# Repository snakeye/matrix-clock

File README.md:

matrix-clock
============

Bedroom clock using 8x8 LED matrix display

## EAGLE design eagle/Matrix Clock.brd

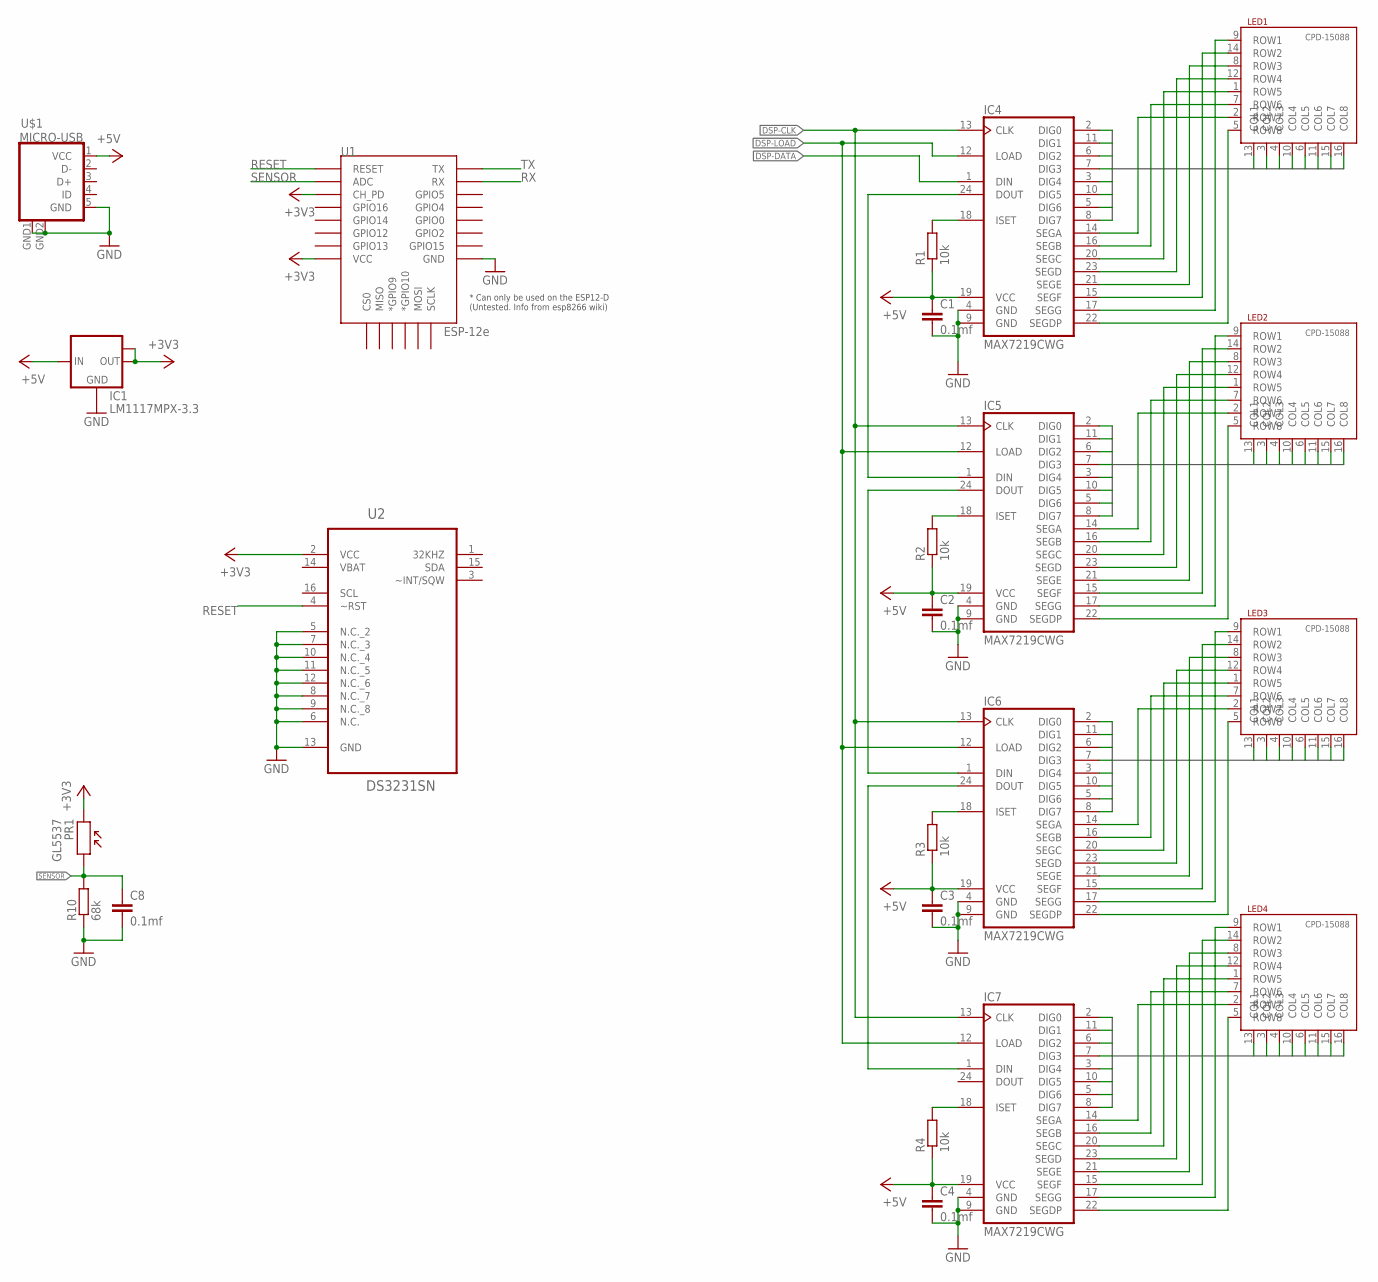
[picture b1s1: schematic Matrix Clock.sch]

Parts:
C1, C2, C3, C4, C8: 0.1mf; C0805
IC1: LM1117MPX-3.3; SOT223
IC4, IC5, IC6, IC7: MAX7219CWG; SO24L
LED1, LED2, LED3, LED4: CPD-15088YGD2/A; CPD15088
PR1: GL5537; GL55
R1, R2, R3, R4: 10k; R0805
R10: 68k; R0805
U1: ESP-12e; ESP12E-SMD
U2: DS3231SN; SOIC127P1032X265-16N
U$1: MICRO-USB

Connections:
+3V3: IC1.2 (OUT), IC1.TAB (OUT1), PR1.P$1, U1.CH_PD, U1.VCC, U2.2 (VCC)
+5V: C1.1, C2.1, C3.1, C4.1, IC1.3 (IN), IC4.19 (VCC), IC5.19 (VCC), IC6.19 (VCC), IC7.19 (VCC), R1.1, R2.1, R3.1, R4.1, U$1.1 (VCC)
C0: IC4.2 (DIG0), LED1.13 (COL1)
C1: IC4.11 (DIG1), LED1.3 (COL2)
C2: IC4.6 (DIG2), LED1.4 (COL3)
C3: IC4.7 (DIG3), LED1.10 (COL4)
C4: IC4.3 (DIG4), LED1.6 (COL5)
C5: IC4.10 (DIG5), LED1.11 (COL6)
C6: IC4.5 (DIG6), LED1.15 (COL7)
C7: IC4.8 (DIG7), LED1.16 (COL8)
C8: IC5.2 (DIG0), LED2.13 (COL1)
C9: IC5.11 (DIG1), LED2.3 (COL2)
C10: IC5.6 (DIG2), LED2.4 (COL3)
C11: IC5.7 (DIG3), LED2.10 (COL4)
C12: IC5.3 (DIG4), LED2.6 (COL5)
C13: IC5.10 (DIG5), LED2.11 (COL6)
C14: IC5.5 (DIG6), LED2.15 (COL7)
C15: IC5.8 (DIG7), LED2.16 (COL8)
C16: IC6.2 (DIG0), LED3.13 (COL1)
C17: IC6.11 (DIG1), LED3.3 (COL2)
C18: IC6.6 (DIG2), LED3.4 (COL3)
C19: IC6.7 (DIG3), LED3.10 (COL4)
C20: IC6.3 (DIG4), LED3.6 (COL5)
C21: IC6.10 (DIG5), LED3.11 (COL6)
C22: IC6.5 (DIG6), LED3.15 (COL7)
C23: IC6.8 (DIG7), LED3.16 (COL8)
C24: IC7.2 (DIG0), LED4.13 (COL1)
C25: IC7.11 (DIG1), LED4.3 (COL2)
C26: IC7.6 (DIG2), LED4.4 (COL3)
C27: IC7.7 (DIG3), LED4.10 (COL4)
C28: IC7.3 (DIG4), LED4.6 (COL5)
C29: IC7.10 (DIG5), LED4.11 (COL6)
C30: IC7.5 (DIG6), LED4.15 (COL7)
C31: IC7.8 (DIG7), LED4.16 (COL8)
DSP-CLK: IC4.13 (CLK), IC5.13 (CLK), IC6.13 (CLK), IC7.13 (CLK)
DSP-DATA: IC4.1 (DIN)
DSP-LOAD: IC4.12 (LOAD), IC5.12 (LOAD), IC6.12 (LOAD), IC7.12 (LOAD)
GND: C1.2, C2.2, C3.2, C4.2, C8.2, IC1.1 (GND), IC4.4 (GND), IC4.9 (GND), IC5.4 (GND), IC5.9 (GND), IC6.4 (GND), IC6.9 (GND), IC7.4 (GND), IC7.9 (GND), R10.1, U1.GND, U2.5 (N.C._2), U2.6 (N.C.), U2.7 (N.C._3), U2.8 (N.C._7), U2.9 (N.C._8), U2.10 (N.C._4), U2.11 (N.C._5), U2.12 (N.C._6), U2.13 (GND), U$1.5 (GND), U$1.GND1 (GND), U$1.GND2 (GND)
unnamed: IC4.22 (SEGDP), LED1.5 (ROW8)
unnamed: IC4.18 (ISET), R1.2
unnamed: IC4.17 (SEGG), LED1.9 (ROW1)
unnamed: IC4.15 (SEGF), LED1.14 (ROW2)
unnamed: IC4.21 (SEGE), LED1.8 (ROW3)
unnamed: IC4.23 (SEGD), LED1.12 (ROW4)
unnamed: IC4.20 (SEGC), LED1.1 (ROW5)
unnamed: IC4.16 (SEGB), LED1.7 (ROW6)
unnamed: IC4.14 (SEGA), LED1.2 (ROW7)
unnamed: IC5.18 (ISET), R2.2
unnamed: IC5.24 (DOUT), IC6.1 (DIN)
unnamed: IC6.24 (DOUT), IC7.1 (DIN)
unnamed: IC4.24 (DOUT), IC5.1 (DIN)
unnamed: IC5.22 (SEGDP), LED2.5 (ROW8)
unnamed: IC5.17 (SEGG), LED2.9 (ROW1)
unnamed: IC5.15 (SEGF), LED2.14 (ROW2)
unnamed: IC5.21 (SEGE), LED2.8 (ROW3)
unnamed: IC5.23 (SEGD), LED2.12 (ROW4)
unnamed: IC5.20 (SEGC), LED2.1 (ROW5)
unnamed: IC5.16 (SEGB), LED2.7 (ROW6)
unnamed: IC5.14 (SEGA), LED2.2 (ROW7)
unnamed: IC6.18 (ISET), R3.2
unnamed: IC6.22 (SEGDP), LED3.5 (ROW8)
unnamed: IC6.17 (SEGG), LED3.9 (ROW1)
unnamed: IC6.15 (SEGF), LED3.14 (ROW2)
unnamed: IC6.21 (SEGE), LED3.8 (ROW3)
unnamed: IC6.23 (SEGD), LED3.12 (ROW4)
unnamed: IC6.20 (SEGC), LED3.1 (ROW5)
unnamed: IC6.16 (SEGB), LED3.7 (ROW6)
unnamed: IC6.14 (SEGA), LED3.2 (ROW7)
unnamed: IC7.18 (ISET), R4.2
unnamed: IC7.22 (SEGDP), LED4.5 (ROW8)
unnamed: IC7.17 (SEGG), LED4.9 (ROW1)
unnamed: IC7.15 (SEGF), LED4.14 (ROW2)
unnamed: IC7.21 (SEGE), LED4.8 (ROW3)
unnamed: IC7.23 (SEGD), LED4.12 (ROW4)
unnamed: IC7.20 (SEGC), LED4.1 (ROW5)
unnamed: IC7.16 (SEGB), LED4.7 (ROW6)
unnamed: IC7.14 (SEGA), LED4.2 (ROW7)
RESET: U1.RESET, U2.4 (~RST)
RX: U1.RXD0 (RX)
SENSOR: C8.1, PR1.P$2, R10.2, U1.ADC
TX: U1.TXD0 (TX)
VBAT: U2.14 (VBAT)

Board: 2 copper layers, 23 parts (8 on the bottom side), 78 nets, no tracks yet.

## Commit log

2013-12-09 REV A
2013-12-09 Project description
2014-01-19 Started clock firmware
2014-01-19 no message
2014-01-20 Default charset
2014-01-24 Draw string function
    - Draw string function
    - Interrupt based brightness handling
    - Small charset update
2014-01-24 Updated charset
2014-01-24 Brightness measurement
    - Added placeholders for peripheral devices
    - Added int to string conversion function
2014-01-25 Big update
    - Asyncronous USART operations
    - Asyncronous ADC
    - Updated schematics file and PCB
2014-01-25 Added buttons processing
2014-01-26 REV A Beta 1
    Beta 1 Firmware for REV A board
2014-02-01 Added new charset, small refactorings
2014-02-02 Fixed terminal response
    Fixed terminal response
    Added "Say" command
2014-02-08 Even better charset
2014-02-23 Updated schematics and board
2014-03-16 Added schematic and board images, pictures of working clock
2014-03-16 Create gh-pages branch via GitHub
2014-03-16 GA tracking
2014-05-18 UART module refactoring
2014-05-27 Added script to set up time via bluetooth
2015-05-03 Added watchdog timer
2016-10-31 Moving to GPS settings
2017-07-24 Esp8266 started
2017-08-03 mongoose os application init
2017-11-11 Removed outdated elements
